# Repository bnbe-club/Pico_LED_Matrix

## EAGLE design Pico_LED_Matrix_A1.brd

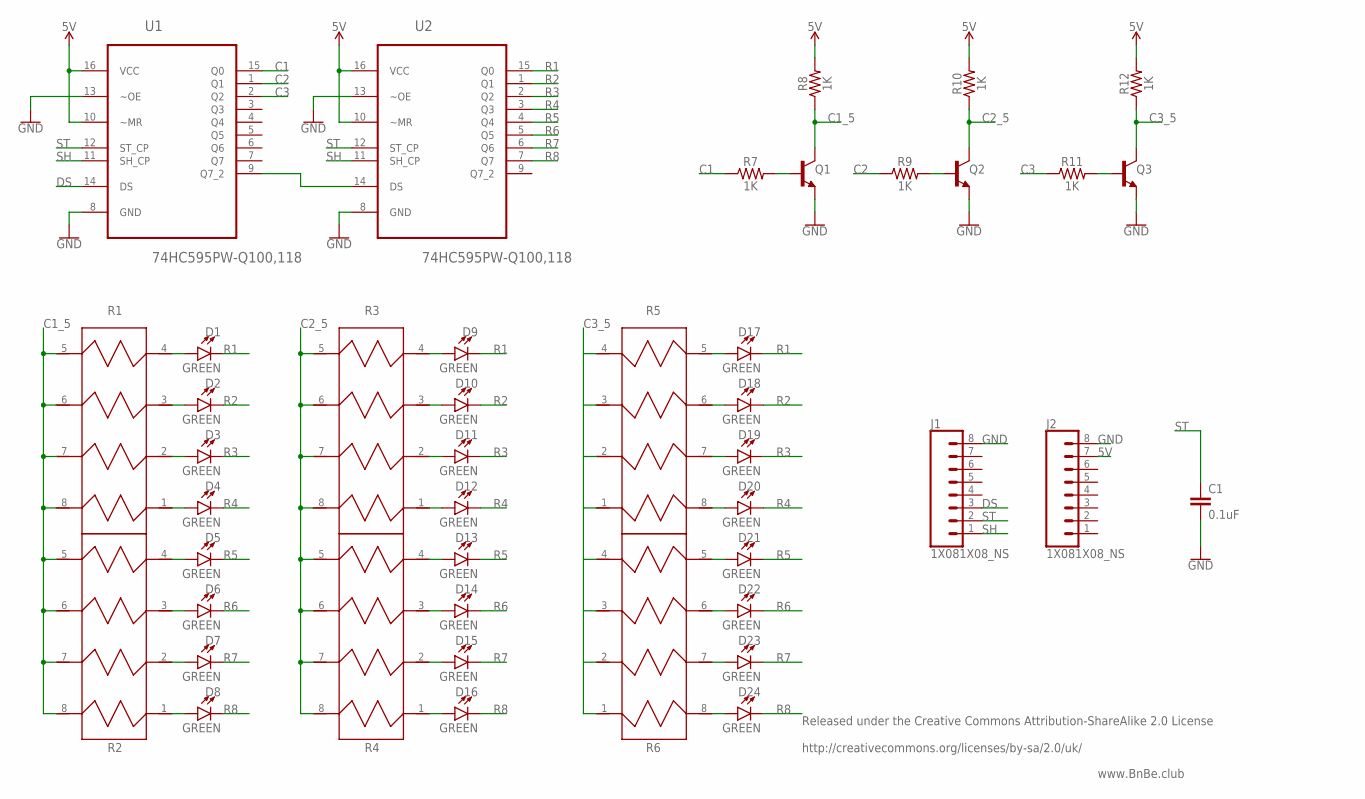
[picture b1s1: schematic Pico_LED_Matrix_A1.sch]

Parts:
C1: 0.1uF; 0402
D1, D2, D3, D4, D5, D6, D7, D8, D9, D10, D11, D12, D13, D14, D15, D16, D17, D18, D19, D20, D21, D22, D23, D24: GREEN; LED-0603
J1, J2: 1X081X08_NS; 1X08_NS
Q1, Q2, Q3: TRANS_NPN-MMBT2222AL; SOT23-3
R1, R2, R3, R4, R5, R6: EXBN8V220JX; RESCAV50P200X100X55-8N
R7, R8, R9, R10, R11, R12: 1K; 0402
U1, U2: 74HC595PW-Q100,118; SOP65P640X110-16N

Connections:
5V: J2.7, R8.2, R10.2, R12.2, U1.10 (~MR), U1.16 (VCC), U2.10 (~MR), U2.16 (VCC)
C1: R7.1, U1.15 (Q0)
C1_5: Q1.3 (C), R1.5, R1.6, R1.7, R1.8, R2.5, R2.6, R2.7, R2.8, R8.1
C2: R9.1, U1.1 (Q1)
C2_5: Q2.3 (C), R3.5, R3.6, R3.7, R3.8, R4.5, R4.6, R4.7, R4.8, R10.1
C3: R11.1, U1.2 (Q2)
C3_5: Q3.3 (C), R5.1, R5.2, R5.3, R5.4, R6.1, R6.2, R6.3, R6.4, R12.1
DS: J1.3, U1.14 (DS)
GND: C1.2, J1.8, J2.8, Q1.2 (E), Q2.2 (E), Q3.2 (E), U1.8 (GND), U1.13 (~OE), U2.8 (GND), U2.13 (~OE)
unnamed: D2.A, R1.3
unnamed: D3.A, R1.2
unnamed: D4.A, R1.1
unnamed: D5.A, R2.4
unnamed: D6.A, R2.3
unnamed: D7.A, R2.2
unnamed: D8.A, R2.1
unnamed: D9.A, R3.4
unnamed: D10.A, R3.3
unnamed: D11.A, R3.2
unnamed: D12.A, R3.1
unnamed: D13.A, R4.4
unnamed: D14.A, R4.3
unnamed: D15.A, R4.2
unnamed: D16.A, R4.1
unnamed: D17.A, R5.5
unnamed: D18.A, R5.6
unnamed: D19.A, R5.7
unnamed: D20.A, R5.8
unnamed: D21.A, R6.5
unnamed: D22.A, R6.6
unnamed: D23.A, R6.7
unnamed: D24.A, R6.8
unnamed: D1.A, R1.4
unnamed: U1.9 (Q7_2), U2.14 (DS)
unnamed: Q1.1 (B), R7.2
unnamed: Q2.1 (B), R9.2
unnamed: Q3.1 (B), R11.2
R1: D1.C, D9.C, D17.C, U2.15 (Q0)
R2: D2.C, D10.C, D18.C, U2.1 (Q1)
R3: D3.C, D11.C, D19.C, U2.2 (Q2)
R4: D4.C, D12.C, D20.C, U2.3 (Q3)
R5: D5.C, D13.C, D21.C, U2.4 (Q4)
R6: D6.C, D14.C, D22.C, U2.5 (Q5)
R7: D7.C, D15.C, D23.C, U2.6 (Q6)
R8: D8.C, D16.C, D24.C, U2.7 (Q7)
SH: J1.1, U1.11 (SH_CP), U2.11 (SH_CP)
ST: C1.1, J1.2, U1.12 (ST_CP), U2.12 (ST_CP)

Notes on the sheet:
www.BnBe.club
Released under the Creative Commons Attribution-ShareAlike 2.0 License http://creativecommons.org/licenses/by-sa/2.0/uk/

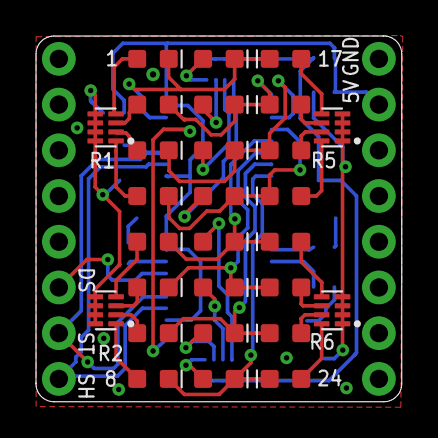
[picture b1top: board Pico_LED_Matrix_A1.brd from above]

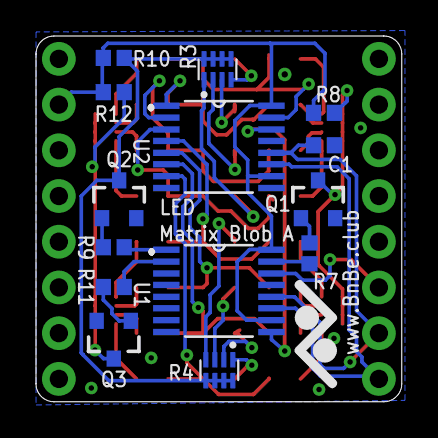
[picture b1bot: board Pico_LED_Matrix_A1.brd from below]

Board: 2 copper layers, 20.3 x 20.3 mm, 44 parts (14 on the bottom side), 47 nets.

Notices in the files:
parts and their libraries:
SparkFun-LED: Licensing: Creative Commons ShareAlike 4.0 International - https://creativecommons.org/licenses/by-sa/4.0
